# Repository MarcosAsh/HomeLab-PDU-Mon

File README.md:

# HomeLab PDU Mon

A 1U 10" rack USB-C power unit for a mini PC homelab: one C14 mains inlet, a Mean Well HRP-300-24
inside, and 6 USB-C PD ports (65 W each), each with its own eFuse and power monitor, plus a
W5500-EVB-Pico that serves Prometheus metrics and can power-cycle any port.

Fork of [Shrike Lab HomeLab-PDU-V1](https://github.com/Shrike-Lab/HomeLab-PDU-V1)
(CERN-OHL-S-2.0). This fork is CERN-OHL-S-2.0 too: if you share or sell it, share the sources.

Marcos Ashton Iglesias, 2026-10-28.

## Layout

| Path | What |
|---|---|
| `SPEC.md` | Design spec: mechanical frame, power path, values, pinout, connectors |
| `pcb/gen.py` | Board generator: parts and nets tables, placement, autoroute, pours, DRC, Gerbers |
| `pcb/jlcpcb/make_jlc.py` | JLCPCB BOM and CPL from the board, with a live stock check |
| `enclosure/enclosure.py` | Sheet-metal enclosure (build123d): tray, lid, front, rear, assembly, marking DXF |
| `firmware/` | Rust/Embassy firmware: Prometheus metrics and per-port switching over Ethernet |
| `datasheets/` | Links to the HRP-300, TPS1663, INA237 and LMR16006 datasheets |

## Rebuild

```
cd pcb && python3 gen.py              # board, routing cached until placement or nets change
python3 jlcpcb/make_jlc.py            # BOM, CPL, parts_check.csv, assembly_note.txt
cd .. && .venv/bin/python enclosure/enclosure.py
```

`gen.py` needs KiCad 9 (pcbnew Python and kicad-cli) and Java for freerouting. The enclosure
script needs build123d, installed in `.venv` (`uv venv .venv && uv pip install -p .venv/bin/python build123d`).

## Ordering

- PCB and assembly, JLCPCB: `pcb/pdu_jlcpcb_gerbers.zip`, `pcb/jlcpcb/jlc_bom.csv`, `pcb/jlcpcb/jlc_cpl.csv`.
  4 layers (In1 solid GND), 1.6 mm, **2 oz outer copper**. Check part rotations in JLC's placement preview.
- Enclosure, JLCCNC sheet metal (5052 aluminium): `enclosure/*.step`, laser marking from
  `enclosure/marking.dxf`. See `enclosure/README.md` for finishes, hardware and the floor-screw decision.
- Bought separately: Mean Well HRP-300-24, 6 x XPM52C 65 W USB-C PD modules, W5500-EVB-Pico,
  C14 3-in-1 inlet (fuse + switch), 16 mm latching button, 40 mm 4-pin fan, RJ45 keystone coupler
  and short patch lead, Molex Mini-Fit Jr harnesses (see the original repo's harness drawings).

## Safety

Mains is only inside the Mean Well and on the inlet wiring. The case must be earthed: IEC earth
and HRP FG to the floor earth stud. Anodising insulates, so mask the earth stud area. Don't power
it with the lid off.

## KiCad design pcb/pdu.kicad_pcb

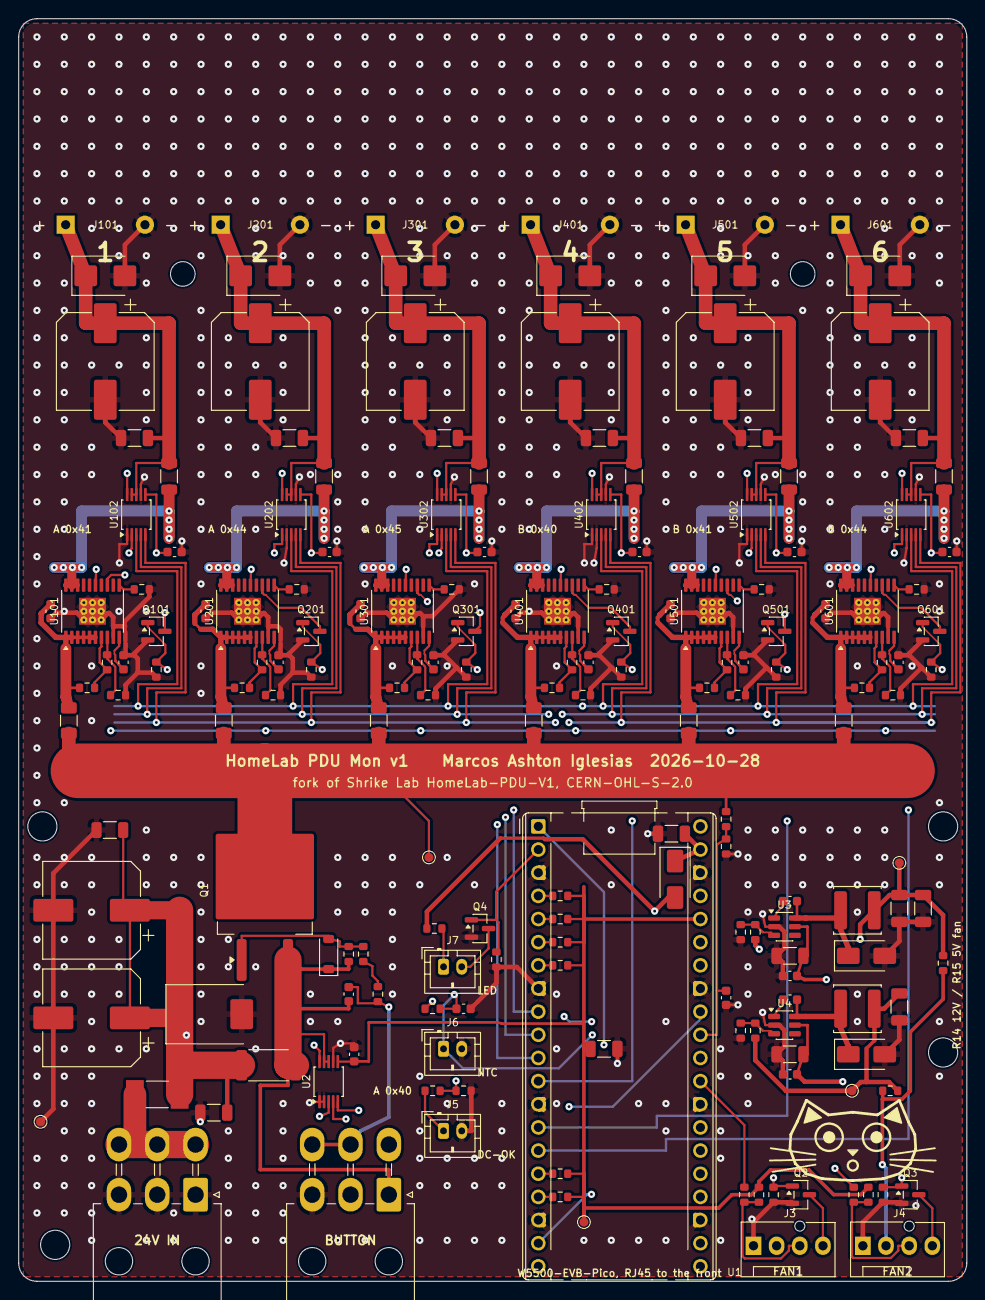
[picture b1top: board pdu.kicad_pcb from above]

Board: 4 copper layers, 104.0 x 138.5 mm, 184 parts (0 on the bottom side), 95 nets.

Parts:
C1, C2, C104, C204, C304, C404, C504, C604: 470u; CP_Elec_10x10.5
C3, C105, C205, C305, C405, C505, C605: 1u; C_1206_3216Metric
C5, C7, C9, C10, C14, C15, C18, C101, C103, C201, C203, C301, C303, C401, C403, C501, C503, C601, C603: 100n; C_0603_1608Metric
C6: 220n; C_0603_1608Metric
C8, C13: 2u2; C_1206_3216Metric
C11, C12, C16: 22u; C_1206_3216Metric
C19, C20: 10u; C_1206_3216Metric
C102, C202, C302, C402, C502, C602: 56n; C_0603_1608Metric
D1: SMCJ26A; D_SMC
D2: 12V; D_SOD-123
D3, D4, D5: SS14; D_SMA
D101, D201, D301, D401, D501, D601: SMBJ26A; D_SMB
F1: 15A; Fuse_Littelfuse-NANO2-451_453
F101, F201, F301, F401, F501, F601: 5A; Fuse_1206_3216Metric
H1, H2: M2.5; MountingHole_2.7mm_M2.5
H3, H4, H5, H6: M3; MountingHole_3.2mm_M3
J1: 24V IN; Molex_Mini-Fit_Jr_5569-06A2_2x03_P4.20mm_Horizontal
J2: BUTTON; Molex_Mini-Fit_Jr_5569-06A2_2x03_P4.20mm_Horizontal
J3: FAN1; FanPinHeader_1x04_P2.54mm_Vertical
J4: FAN2; FanPinHeader_1x04_P2.54mm_Vertical
J5: DC-OK; JST_PH_B2B-PH-K_1x02_P2.00mm_Vertical
J6: NTC; JST_PH_B2B-PH-K_1x02_P2.00mm_Vertical
J7: LED; JST_PH_B2B-PH-K_1x02_P2.00mm_Vertical
J101: PD1; PD_Module_XPM52C_Standing
J201: PD2; PD_Module_XPM52C_Standing
J301: PD3; PD_Module_XPM52C_Standing
J401: PD4; PD_Module_XPM52C_Standing
J501: PD5; PD_Module_XPM52C_Standing
J601: PD6; PD_Module_XPM52C_Standing
L1: 33u; L_Sunlord_SWPA5040S
L2: 47u; L_Sunlord_SWPA5040S
Q1: NCEP40PT15D; TO-263-2
Q2, Q3, Q4, Q101, Q201, Q301, Q401, Q501, Q601: 2N7002; SOT-23
R1: 4k7; R_1206_3216Metric
R2: 2m; R_2512_6332Metric
R3: 47k; R_0603_1608Metric
R4: 100R; R_0603_1608Metric
R5, R6, R16, R19, R26, R105, R205, R305, R405, R505, R605: 100k; R_0603_1608Metric
R7, R10, R12, R17, R20, R24, R29, R30: 10k; R_0603_1608Metric
R9: 56k; R_0603_1608Metric
R11: 147k; R_0603_1608Metric
R14, R15: 0R; R_0603_1608Metric
R18, R21: 1k; R_0603_1608Metric
R22: 15k; R_0603_1608Metric
R23, R104, R204, R304, R404, R504, R604: 20k; R_0603_1608Metric
R25: 220R; R_0603_1608Metric
R27, R28, R31, R32: 4k7; R_0603_1608Metric
R101, R201, R301, R401, R501, R601: 4k53; R_0603_1608Metric
R102, R202, R302, R402, R502, R602: 442k; R_0603_1608Metric
R103, R203, R303, R403, R503, R603: 8k06; R_0603_1608Metric
R106, R206, R306, R406, R506, R606: 10m; R_1206_3216Metric
TP1: GND; TestPoint_Pad_D1.0mm
TP2: +5V; TestPoint_Pad_D1.0mm
TP3: +3V3; TestPoint_Pad_D1.0mm
TP4: +12V; TestPoint_Pad_D1.0mm
TP5: +24V_SW; TestPoint_Pad_D1.0mm
U1: W5500-EVB-Pico; RaspberryPi_Pico_Common_THT
U2, U102, U202, U302, U402, U502, U602: INA237; VSSOP-10_3x3mm_P0.5mm
U3, U4: LMR16006X; TSOT-23-6
U101, U201, U301, U401, U501, U601: TPS16630; HTSSOP-20-1EP_4.4x6.5mm_P0.65mm_EP2.96x2.96mm_ThermalVias

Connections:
+3V3: C5.1, C20.2, C103.1, C203.1, C303.1, C403.1, C503.1, C603.1, R17.2, R20.2, R27.2, R28.2, R29.2, R30.2, R31.2, R32.2, TP3.1, U1.36, U2.6, U102.2, U102.6, U202.1, U202.6, U302.1, U302.2, U302.6, U402.6, U502.2, U502.6, U602.1, U602.6
+5V: C11.2, C12.2, D4.2, L1.2, R9.1, R15.2, R25.1, TP2.1
+12V: C16.2, L2.2, R11.1, R14.2, TP4.1
+24V: C6.1, C8.2, C9.2, C13.2, C14.2, D2.1, J2.1, Q1.3, R2.1, R5.2, U2.8, U2.9, U3.5, U4.5
+24V_F: C1.1, C2.1, C3.2, D1.1, F1.2, R1.2, R2.2, U2.10
+24V_RAW: F1.1, J1.4, J1.5, J1.6
+24V_SW: F101.1, F201.1, F301.1, F401.1, F501.1, F601.1, Q1.2, R6.2, TP5.1
ADC_VREF: R24.1, U1.35
ALERT_N: R30.1, U1.17, U2.3, U102.3, U202.3, U302.3, U402.3, U502.3, U602.3
B5_CB: C10.1, U3.1
B5_FB: R9.2, R10.2, U3.3
B5_SW: C10.2, D3.1, L1.1, U3.6
B12_CB: C15.1, U4.1
B12_FB: R11.2, R12.2, U4.3
B12_SW: C15.2, D5.1, L2.1, U4.6
BTN: C6.2, J2.5, J2.6, R3.2
DCOK: R22.2, R23.1, U1.32
DCOK_IN: J5.1, R22.1
FAN1_PWM: J3.4, Q2.3
FAN1_PWMC: Q2.1, R16.2, U1.19
FAN1_TACH: R18.2, U1.29
FAN1_TACHR: J3.3, R17.1, R18.1
FAN2_PWM: J4.4, Q3.3
FAN2_PWMC: Q3.1, R19.2, U1.20
FAN2_TACH: R21.2, U1.1
FAN2_TACHR: J4.3, R20.1, R21.1
FLT_N: R29.1, U1.16, U101.15, U201.15, U301.15, U401.15, U501.15, U601.15
GND: C1.2, C2.2, C3.1, C5.2, C7.1, C8.1, C9.1, C11.1, C12.1, C13.1, C14.1, C16.1, C18.2, C19.1, C20.1, C101.1, C102.2, C103.2, C104.2, C105.1, C201.1, C202.2, C203.2, C204.2, C205.1, C301.1, C302.2, C303.2, C304.2, C305.1, C401.1, C402.2, C403.2, C404.2, C405.1, C501.1, C502.2, C503.2, C504.2, C505.1, C601.1, C602.2, C603.2, C604.2, C605.1, D1.2, D3.2, D5.2, D101.2, D201.2, D301.2, D401.2, D501.2, D601.2, J1.1, J1.2, J1.3, J2.3, J3.1, J4.1, J5.2, J6.2, J101.2, J201.2, J301.2, J401.2, J501.2, J601.2, Q2.2, Q3.2, Q4.2, Q101.2, Q201.2, Q301.2, Q401.2, Q501.2, Q601.2, R1.1, R7.1, R10.1, R12.1, R16.1, R19.1, R23.2, R26.1, R101.2, R104.2, R105.1, R201.2, R204.2, R205.1, R301.2, R304.2, R305.1, R401.2, R404.2, R405.1, R501.2, R504.2, R505.1, R601.2, R604.2, R605.1, TP1.1, U1.3, U1.8, U1.13, U1.18, U1.23, U1.28, U1.33, U1.38, U2.1, U2.2, U2.7, U3.2, U4.2, U101.9, U101.21, U102.1, U102.7, U201.9, U201.21, U202.2, U202.7, U301.9, U301.21, U302.7, U401.9, U401.21, U402.1, U402.2, U402.7, U501.9, U501.21, U502.1, U502.7, U601.9, U601.21, U602.2, U602.7
LED_A: J7.1, R25.2
LED_CTL: Q4.1, R26.2, U1.2
LED_K: J7.2, Q4.3
NTC: C18.1, J6.1, R24.2, U1.34
P1_DVDT: C102.1, U101.10
P1_EF: R106.1, U101.18, U101.19, U101.20, U102.10
P1_ILIM: R101.1, U101.11
P1_IN: C101.2, F101.2, R102.1, U101.1, U101.2, U101.3, U101.4, U101.5, U101.6
P1_OFF: Q101.1, R105.2, U1.11
P1_OUT: C104.1, C105.2, D101.1, J101.1, R106.2, U102.8, U102.9
P1_OVP: R103.2, R104.1, U101.8
P1_SHDN: Q101.3, U101.13
P1_UVLO: R102.2, R103.1, U101.7
P2_DVDT: C202.1, U201.10
P2_EF: R206.1, U201.18, U201.19, U201.20, U202.10
P2_ILIM: R201.1, U201.11
P2_IN: C201.2, F201.2, R202.1, U201.1, U201.2, U201.3, U201.4, U201.5, U201.6
P2_OFF: Q201.1, R205.2, U1.10
P2_OUT: C204.1, C205.2, D201.1, J201.1, R206.2, U202.8, U202.9
P2_OVP: R203.2, R204.1, U201.8
P2_SHDN: Q201.3, U201.13
P2_UVLO: R202.2, R203.1, U201.7
P3_DVDT: C302.1, U301.10
P3_EF: R306.1, U301.18, U301.19, U301.20, U302.10
P3_ILIM: R301.1, U301.11
P3_IN: C301.2, F301.2, R302.1, U301.1, U301.2, U301.3, U301.4, U301.5, U301.6
P3_OFF: Q301.1, R305.2, U1.9
P3_OUT: C304.1, C305.2, D301.1, J301.1, R306.2, U302.8, U302.9
P3_OVP: R303.2, R304.1, U301.8
P3_SHDN: Q301.3, U301.13
P3_UVLO: R302.2, R303.1, U301.7
P4_DVDT: C402.1, U401.10
P4_EF: R406.1, U401.18, U401.19, U401.20, U402.10
P4_ILIM: R401.1, U401.11
P4_IN: C401.2, F401.2, R402.1, U401.1, U401.2, U401.3, U401.4, U401.5, U401.6
P4_OFF: Q401.1, R405.2, U1.12
P4_OUT: C404.1, C405.2, D401.1, J401.1, R406.2, U402.8, U402.9
P4_OVP: R403.2, R404.1, U401.8
P4_SHDN: Q401.3, U401.13
P4_UVLO: R402.2, R403.1, U401.7
P5_DVDT: C502.1, U501.10
P5_EF: R506.1, U501.18, U501.19, U501.20, U502.10
P5_ILIM: R501.1, U501.11
P5_IN: C501.2, F501.2, R502.1, U501.1, U501.2, U501.3, U501.4, U501.5, U501.6
P5_OFF: Q501.1, R505.2, U1.14
P5_OUT: C504.1, C505.2, D501.1, J501.1, R506.2, U502.8, U502.9
P5_OVP: R503.2, R504.1, U501.8
P5_SHDN: Q501.3, U501.13
P5_UVLO: R502.2, R503.1, U501.7
P6_DVDT: C602.1, U601.10
P6_EF: R606.1, U601.18, U601.19, U601.20, U602.10
P6_ILIM: R601.1, U601.11
P6_IN: C601.2, F601.2, R602.1, U601.1, U601.2, U601.3, U601.4, U601.5, U601.6
P6_OFF: Q601.1, R605.2, U1.15
P6_OUT: C604.1, C605.2, D601.1, J601.1, R606.2, U602.8, U602.9
P6_OVP: R603.2, R604.1, U601.8
P6_SHDN: Q601.3, U601.13
P6_UVLO: R602.2, R603.1, U601.7
Q1_G: D2.2, Q1.1, R4.1, R5.1
Q1_GR: R3.1, R4.2
SCL: R28.1, U1.5, U2.5, U102.5, U202.5, U302.5
SCL_B: R32.1, U1.7, U402.5, U502.5, U602.5
SDA: R27.1, U1.4, U2.4, U102.4, U202.4, U302.4
SDA_B: R31.1, U1.6, U402.4, U502.4, U602.4
SW_SENSE: C7.2, R6.1, R7.2, U1.31
VFAN: J3.2, J4.2, R14.1, R15.1
VSYS: C19.2, D4.1, U1.39

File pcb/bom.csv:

qty,refs,value,description,LCSC,footprint,fit
2,C1 C2,470u,"470 uF 35 V, input",C976030,Capacitor_SMD:CP_Elec_10x10.5,fit
2,C10 C15,100n,boot cap,C14663,Capacitor_SMD:C_0603_1608Metric,fit
6,C101 C201 C301 C401 C501 C601,100n,"100 nF 50 V, eFuse IN",C14663,Capacitor_SMD:C_0603_1608Metric,fit
6,C102 C202 C302 C402 C502 C602,56n,C_dVdT 56 nF: 28 ms ramp,C282072,Capacitor_SMD:C_0603_1608Metric,fit
7,C103 C203 C303 C403 C503 C603 C5,100n,"100 nF, INA237 VS",C14663,Capacitor_SMD:C_0603_1608Metric,fit
6,C104 C204 C304 C404 C504 C604,470u,"470 uF 35 V, port output",C976030,Capacitor_SMD:CP_Elec_10x10.5,fit
6,C105 C205 C305 C405 C505 C605,1u,"1 uF 50 V X7R, port output",C1848,Capacitor_SMD:C_1206_3216Metric,fit
2,C11 C12,22u,"22 uF 25 V X5R, 5 V out",C12891,Capacitor_SMD:C_1206_3216Metric,fit
1,C16,22u,"22 uF 25 V X5R, 12 V out",C12891,Capacitor_SMD:C_1206_3216Metric,fit
1,C18,100n,NTC filter,C14663,Capacitor_SMD:C_0603_1608Metric,fit
1,C19,10u,"10 uF 25 V, VSYS (under the module)",C13585,Capacitor_SMD:C_1206_3216Metric,fit
1,C20,10u,"10 uF 25 V, 3V3 (under the module, on the bar)",C13585,Capacitor_SMD:C_1206_3216Metric,fit
1,C3,1u,"1 uF 50 V X7R, input",C1848,Capacitor_SMD:C_1206_3216Metric,fit
1,C6,220n,"220 nF 50 V, soft switch",C64705,Capacitor_SMD:C_0603_1608Metric,fit
1,C7,100n,"24V_SW sense filter, at the Pico pin",C14663,Capacitor_SMD:C_0603_1608Metric,fit
2,C8 C13,2u2,"2.2 uF 50 V X7R, buck input",C50254,Capacitor_SMD:C_1206_3216Metric,fit
2,C9 C14,100n,"100 nF 50 V, buck input",C14663,Capacitor_SMD:C_0603_1608Metric,fit
1,D1,SMCJ26A,"TVS 26 V, input",C152085,Diode_SMD:D_SMC,fit
6,D101 D201 D301 D401 D501 D601,SMBJ26A,"TVS 26 V, port output",C123820,Diode_SMD:D_SMB,fit
1,D2,12V,"zener 12 V, gate clamp (K to source)",C173429,Diode_SMD:D_SOD-123,fit
2,D3 D5,SS14,"Schottky 40 V 1 A, buck catch",C2480,Diode_SMD:D_SMA,fit
1,D4,SS14,Schottky +5V to VSYS (USB on the Pico stays safe),C2480,Diode_SMD:D_SMA,fit
1,F1,15A,fuse 15 A 2410 (Littelfuse 451),C44480,Fuse:Fuse_Littelfuse-NANO2-451_453,fit
6,F101 F201 F301 F401 F501 F601,5A,fuse 5 A 1206 fast,C57525,Fuse:Fuse_1206_3216Metric,fit
1,J1,24V IN,"Mini-Fit Jr 2x3 right angle, from HRP-300 +V/-V",C114098,Connector_Molex:Molex_Mini-Fit_Jr_5569-06A2_2x03_P4.20mm_Horizontal,fit
1,J101,PD1,"XPM52C 65 W USB-C PD module, owner-fitted on 2 pins",,pdu:pdmodule,fit
1,J2,BUTTON,"Mini-Fit Jr 2x3 right angle, latching button (original pinout)",C114098,Connector_Molex:Molex_Mini-Fit_Jr_5569-06A2_2x03_P4.20mm_Horizontal,fit
1,J201,PD2,"XPM52C 65 W USB-C PD module, owner-fitted on 2 pins",,pdu:pdmodule,fit
1,J3,FAN1,4-pin PWM fan header (Molex 47053),C240840,Connector:FanPinHeader_1x04_P2.54mm_Vertical,fit
1,J301,PD3,"XPM52C 65 W USB-C PD module, owner-fitted on 2 pins",,pdu:pdmodule,fit
1,J4,FAN2,4-pin PWM fan header (Molex 47053),C240840,Connector:FanPinHeader_1x04_P2.54mm_Vertical,fit
1,J401,PD4,"XPM52C 65 W USB-C PD module, owner-fitted on 2 pins",,pdu:pdmodule,fit
1,J5,DC-OK,"JST PH 2-pin: HRP CN100 pin 3 DC-OK, pin 5 GND",C5251182,Connector_JST:JST_PH_B2B-PH-K_1x02_P2.00mm_Vertical,fit
1,J501,PD5,"XPM52C 65 W USB-C PD module, owner-fitted on 2 pins",,pdu:pdmodule,fit
1,J6,NTC,JST PH 2-pin: 10 k NTC on the PSU case,C5251182,Connector_JST:JST_PH_B2B-PH-K_1x02_P2.00mm_Vertical,fit
1,J601,PD6,"XPM52C 65 W USB-C PD module, owner-fitted on 2 pins",,pdu:pdmodule,fit
1,J7,LED,"JST PH 2-pin: front status LED (1 anode, 2 cathode)",C5251182,Connector_JST:JST_PH_B2B-PH-K_1x02_P2.00mm_Vertical,fit
1,L1,33u,"33u shielded 5040, buck",C86618,Inductor_SMD:L_Sunlord_SWPA5040S,fit
1,L2,47u,"47u shielded 5040, buck",C86617,Inductor_SMD:L_Sunlord_SWPA5040S,fit
1,Q1,NCEP40PT15D,"P-FET 40 V, master switch",C918237,Package_TO_SOT_SMD:TO-263-2,fit
6,Q101 Q201 Q301 Q401 Q501 Q601,2N7002,port off switch on SHDN,C8545,Package_TO_SOT_SMD:SOT-23,fit
2,Q2 Q3,2N7002,fan PWM open drain,C8545,Package_TO_SOT_SMD:SOT-23,fit
1,Q4,2N7002,LED low side,C8545,Package_TO_SOT_SMD:SOT-23,fit
1,R1,4k7,bleeder 4.7 k 1206,C17936,Resistor_SMD:R_1206_3216Metric,fit
2,R10 R12,10k,FB bottom,C25804,Resistor_SMD:R_0603_1608Metric,fit
6,R101 R201 R301 R401 R501 R601,4k53,R_ILIM 4.53 k 1 %: 3.97 A,C25971,Resistor_SMD:R_0603_1608Metric,fit
6,R102 R202 R302 R402 R502 R602,442k,"UVLO/OVP divider top, 1 %",C23175,Resistor_SMD:R_0603_1608Metric,fit
6,R103 R203 R303 R403 R503 R603,8k06,"UVLO/OVP divider middle, 1 %",C23112,Resistor_SMD:R_0603_1608Metric,fit
6,R104 R204 R304 R404 R504 R604,20k,"UVLO/OVP divider bottom, 1 %",C4184,Resistor_SMD:R_0603_1608Metric,fit
6,R105 R205 R305 R405 R505 R605,100k,port off gate pull-down,C25803,Resistor_SMD:R_0603_1608Metric,fit
6,R106 R206 R306 R406 R506 R606,10m,10 mOhm 1 % 0.5 W shunt,C105362,Resistor_SMD:R_1206_3216Metric,fit
1,R11,147k,FB top,C22878,Resistor_SMD:R_0603_1608Metric,fit
1,R14,0R,fan supply 12 V (fit this or R15),C21189,Resistor_SMD:R_0603_1608Metric,fit
0,R15,0R,fan supply 5 V (DNP by default),C21189,Resistor_SMD:R_0603_1608Metric,DNP
2,R16 R19,100k,PWM gate pull-down (MCU off = full speed),C25803,Resistor_SMD:R_0603_1608Metric,fit
2,R17 R20,10k,tach pull-up,C25804,Resistor_SMD:R_0603_1608Metric,fit
2,R18 R21,1k,tach series,C21190,Resistor_SMD:R_0603_1608Metric,fit
1,R2,2m,2 mOhm 1 % 2512 input shunt,C160590,Resistor_SMD:R_2512_6332Metric,fit
1,R22,15k,DC-OK divider top (5.6 V -> 3.2 V),C22809,Resistor_SMD:R_0603_1608Metric,fit
1,R23,20k,DC-OK divider bottom,C4184,Resistor_SMD:R_0603_1608Metric,fit
1,R24,10k,NTC pull-up to ADC_VREF,C25804,Resistor_SMD:R_0603_1608Metric,fit
1,R25,220R,"LED current, from +5V",C22962,Resistor_SMD:R_0603_1608Metric,fit
1,R26,100k,LED gate pull-down,C25803,Resistor_SMD:R_0603_1608Metric,fit
1,R27,4k7,SDA pull-up,C23162,Resistor_SMD:R_0603_1608Metric,fit
1,R28,4k7,SCL pull-up,C23162,Resistor_SMD:R_0603_1608Metric,fit
1,R29,10k,FLT_N pull-up,C25804,Resistor_SMD:R_0603_1608Metric,fit
1,R3,47k,button to gate,C25819,Resistor_SMD:R_0603_1608Metric,fit
1,R30,10k,ALERT_N pull-up,C25804,Resistor_SMD:R_0603_1608Metric,fit
1,R31,4k7,SDA_B pull-up,C23162,Resistor_SMD:R_0603_1608Metric,fit
1,R32,4k7,SCL_B pull-up,C23162,Resistor_SMD:R_0603_1608Metric,fit
1,R4,100R,gate series,C22775,Resistor_SMD:R_0603_1608Metric,fit
1,R5,100k,gate to source,C25803,Resistor_SMD:R_0603_1608Metric,fit
1,R6,100k,24V_SW sense divider top,C25803,Resistor_SMD:R_0603_1608Metric,fit
1,R7,10k,24V_SW sense divider bottom,C25804,Resistor_SMD:R_0603_1608Metric,fit
1,R9,56k,FB top,C23206,Resistor_SMD:R_0603_1608Metric,fit
1,TP1,GND,test pad GND,,TestPoint:TestPoint_Pad_D1.0mm,fit
1,TP2,+5V,test pad +5V,,TestPoint:TestPoint_Pad_D1.0mm,fit
1,TP3,+3V3,test pad +3V3,,TestPoint:TestPoint_Pad_D1.0mm,fit
1,TP4,+12V,test pad +12V,,TestPoint:TestPoint_Pad_D1.0mm,fit
1,TP5,+24V_SW,test pad +24V_SW,,TestPoint:TestPoint_Pad_D1.0mm,fit
1,U1,W5500-EVB-Pico,"WIZnet W5500-EVB-Pico on 2x 1x20 8.5 mm female headers, owner-fitted",,Module:RaspberryPi_Pico_Common_THT,fit
6,U101 U201 U301 U401 U501 U601,TPS16630,TPS16630 60 V 6 A eFuse,C1849461,pdu:htssop20,fit
1,U102,INA237,"INA237 power monitor, I2C A 0x41",C2864837,Package_SO:VSSOP-10_3x3mm_P0.5mm,fit
1,U2,INA237,"INA237 input monitor, I2C 0x40",C2864837,Package_SO:VSSOP-10_3x3mm_P0.5mm,fit
1,U202,INA237,"INA237 power monitor, I2C A 0x44",C2864837,Package_SO:VSSOP-10_3x3mm_P0.5mm,fit
1,U3,LMR16006X,"LMR16006X 60 V 0.6 A buck, 5V",C87080,Package_TO_SOT_SMD:TSOT-23-6,fit
1,U302,INA237,"INA237 power monitor, I2C A 0x45",C2864837,Package_SO:VSSOP-10_3x3mm_P0.5mm,fit
1,U4,LMR16006X,"LMR16006X 60 V 0.6 A buck, 12V",C87080,Package_TO_SOT_SMD:TSOT-23-6,fit
1,U402,INA237,"INA237 power monitor, I2C B 0x40",C2864837,Package_SO:VSSOP-10_3x3mm_P0.5mm,fit
1,U502,INA237,"INA237 power monitor, I2C B 0x41",C2864837,Package_SO:VSSOP-10_3x3mm_P0.5mm,fit
1,U602,INA237,"INA237 power monitor, I2C B 0x44",C2864837,Package_SO:VSSOP-10_3x3mm_P0.5mm,fit

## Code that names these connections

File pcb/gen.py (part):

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connect("SDA", "R27.1"); connect("+3V3", "R27.2")
part("R28", "R0603", PU_X, pico_pin_y(5), 0, "4k7", "SCL pull-up", "C23162")
connect("SCL", "R28.1"); connect("+3V3", "R28.2")
part("R29", "R0603", PU_X, pico_pin_y(16), 0, "10k", "FLT_N pull-up", "C25804")
connect("FLT_N", "R29.1"); connect("+3V3", "R29.2")
part("R30", "R0603", PU_X, pico_pin_y(17), 0, "10k", "ALERT_N pull-up", "C25804")
connect("ALERT_N", "R30.1"); connect("+3V3", "R30.2")
part("R31", "R0603", PU_X, pico_pin_y(6), 0, "4k7", "SDA_B pull-up", "C23162")
connect("SDA_B", "R31.1"); connect("+3V3", "R31.2")
part("R32", "R0603", PU_X, pico_pin_y(7), 0, "4k7", "SCL_B pull-up", "C23162")
connect("SCL_B", "R32.1"); connect("+3V3", "R32.2")

# ---- aux bucks from +24V (unswitched): 5 V for the Pico, 12 V for the fans (front-right)
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DNP.add("R15")


# ---- fans: 4-pin PWM headers (GND, VFAN, tach, PWM), tach pulled to 3V3, PWM open drain
def fan(k, j, x, y, q, r_pd, r_pu, r_s, tach_net):
    pwm = "FAN%d_PWM" % k
    part(j, "FAN", x, y, 0, "FAN%d" % k, "4-pin PWM fan header (Molex 47053)", "C240840")
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connect("DCOK_IN", "R22.1"); connect("DCOK", "R22.2")
part("R23", "R0603", 48.8, 117.6, 0, "20k", "DC-OK divider bottom", "C4184")
connect("DCOK", "R23.1"); connect("GND", "R23.2")
part("J6", "PH2", 46.6, 113.0, 0, "NTC", "JST PH 2-pin: 10 k NTC on the PSU case", "C5251182")
connect("NTC", "J6.1"); connect("GND", "J6.2")
part("R24", "R0603", 45.4, 108.6, 0, "10k", "NTC pull-up to ADC_VREF", "C25804")
connect("ADC_VREF", "R24.1"); connect("NTC", "R24.2")
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

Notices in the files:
pcb/gen.py:
Fork of Shrike Lab HomeLab-PDU-V1 (CERN-OHL-S-2.0): 6 USB-C PD module ports off a Mean Well
FORK_LINE = "fork of Shrike Lab HomeLab-PDU-V1, CERN-OHL-S-2.0"
